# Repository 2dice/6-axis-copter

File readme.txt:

■6軸コプター概要
6軸に移動可能なマルチコプターを6個のプロペラで実現することを目標としている．
最終的には自動で衝突回避・PCからコマンドを受信しアクロバットな動きをさせる．

■開発フェーズ
ラフ設計段階
・電子回路
	1x基板(コアレス->ブラシモータ)浮力不足により2xでブラシレスモータ試作
	2x基板作成中
・アクチュエータ
	ブラシレスモータ・プロペラ仮選定済み．2xで浮力確認
・ソフトウェア
	デバイスドライバ仮実装完了．
	2x基板作成後最終確認．その後モータ制御実装．
・筐体
	2x向け設計完了(3Dプリント中)

■ディレクトリ構成
./datasheet
	電子回路に使用している部品のデータシート置き場
./devlog
	開発記録
./schematic
	**.sch
		回路図(kicad)
	**.kicad_pcb
		基板図(kicad)
	librarys
		回路図に使用したライブラリ(kicad)
	gbr
		P板.com提出ファイル(板厚0.6mmで発注)
	**.pdf
		回路図
	**.FCStd
		筐体3D-CAD設計ファイル(FreeCAD)
	**.stl
		DMM.make提出ファイル(3Dプリンタ用STLファイル)
./src
	ソフトウェア
	環境構築は以下を参照
	http://qiita.com/2dice/items/70c5abf6259508660bce
./src/tools/6-axis-monitor
	無線通信(zigbee)によるモニタツール(Qt)
	zigbee環境構築方法は作成中

■構成
・プロペラ配置は3d図面及び./devlog/pictureを参照
・ブラシレスモータとリポバッテリ(3セル直列)を使用
・移動量は3軸ジャイロ及び3軸加速度センサでモニタ
・EEPROMにチューニングパラメータを保存
・測距センサを全軸に付け，衝突を回避するようなロジックを入れる
・デバイスの電源電圧の都合上4.5V/3.6Vの2電源を生成．
  本来I/Fにレベルシフタを入れるべきだが抵抗で保護し実力で故障回避を狙う．
  そのため電源電圧を極力近づける設計とした．

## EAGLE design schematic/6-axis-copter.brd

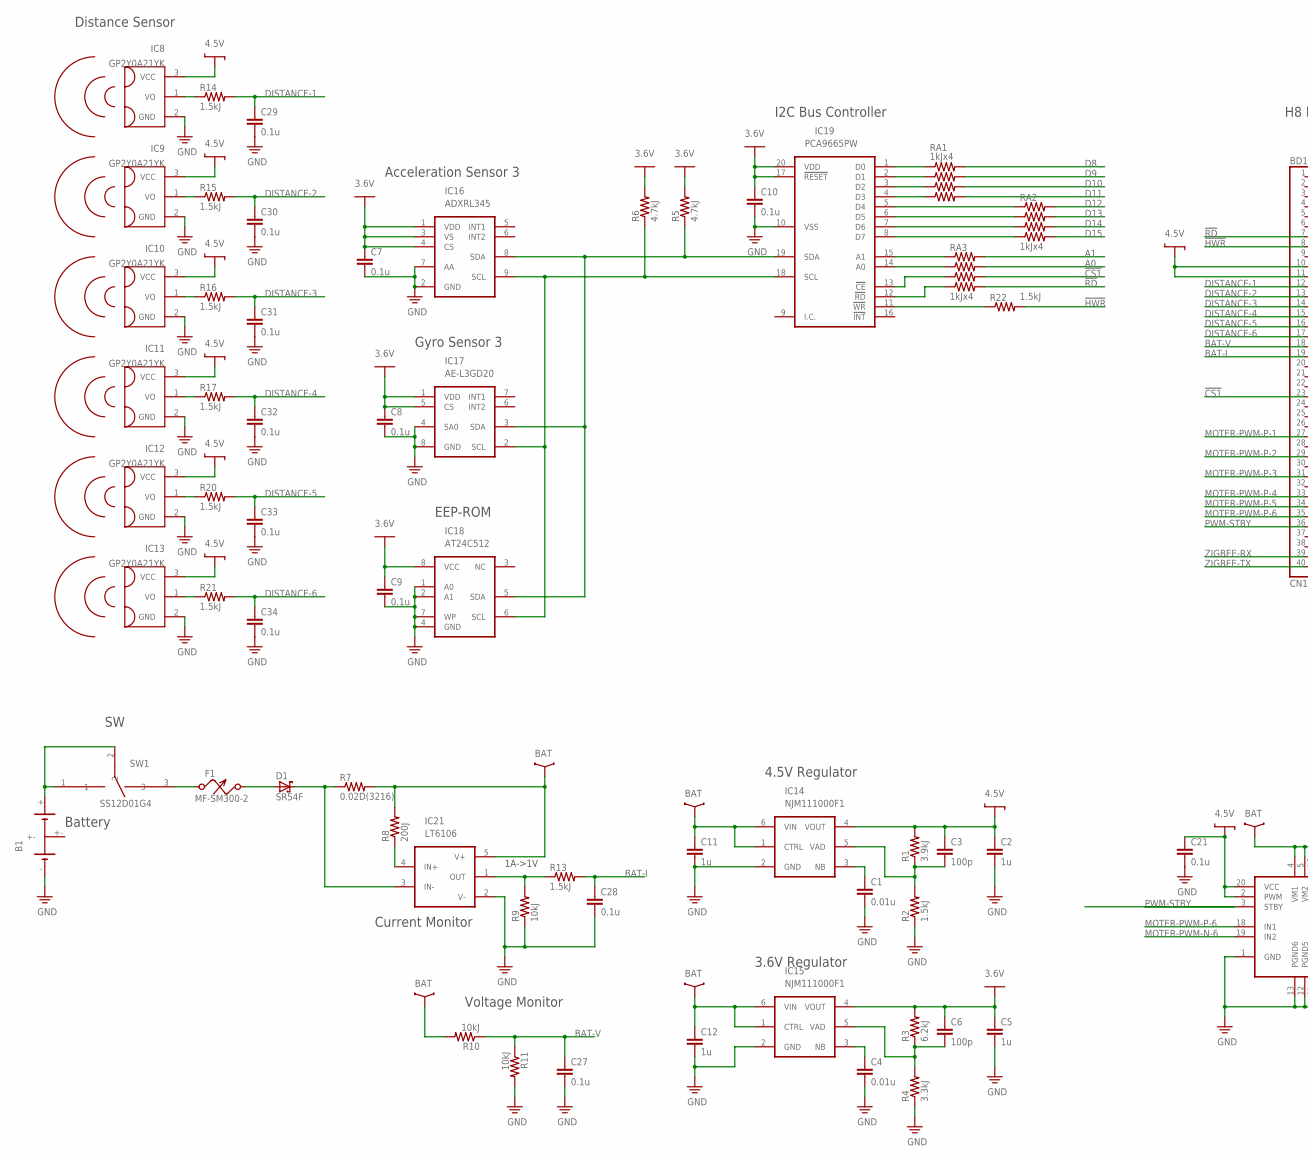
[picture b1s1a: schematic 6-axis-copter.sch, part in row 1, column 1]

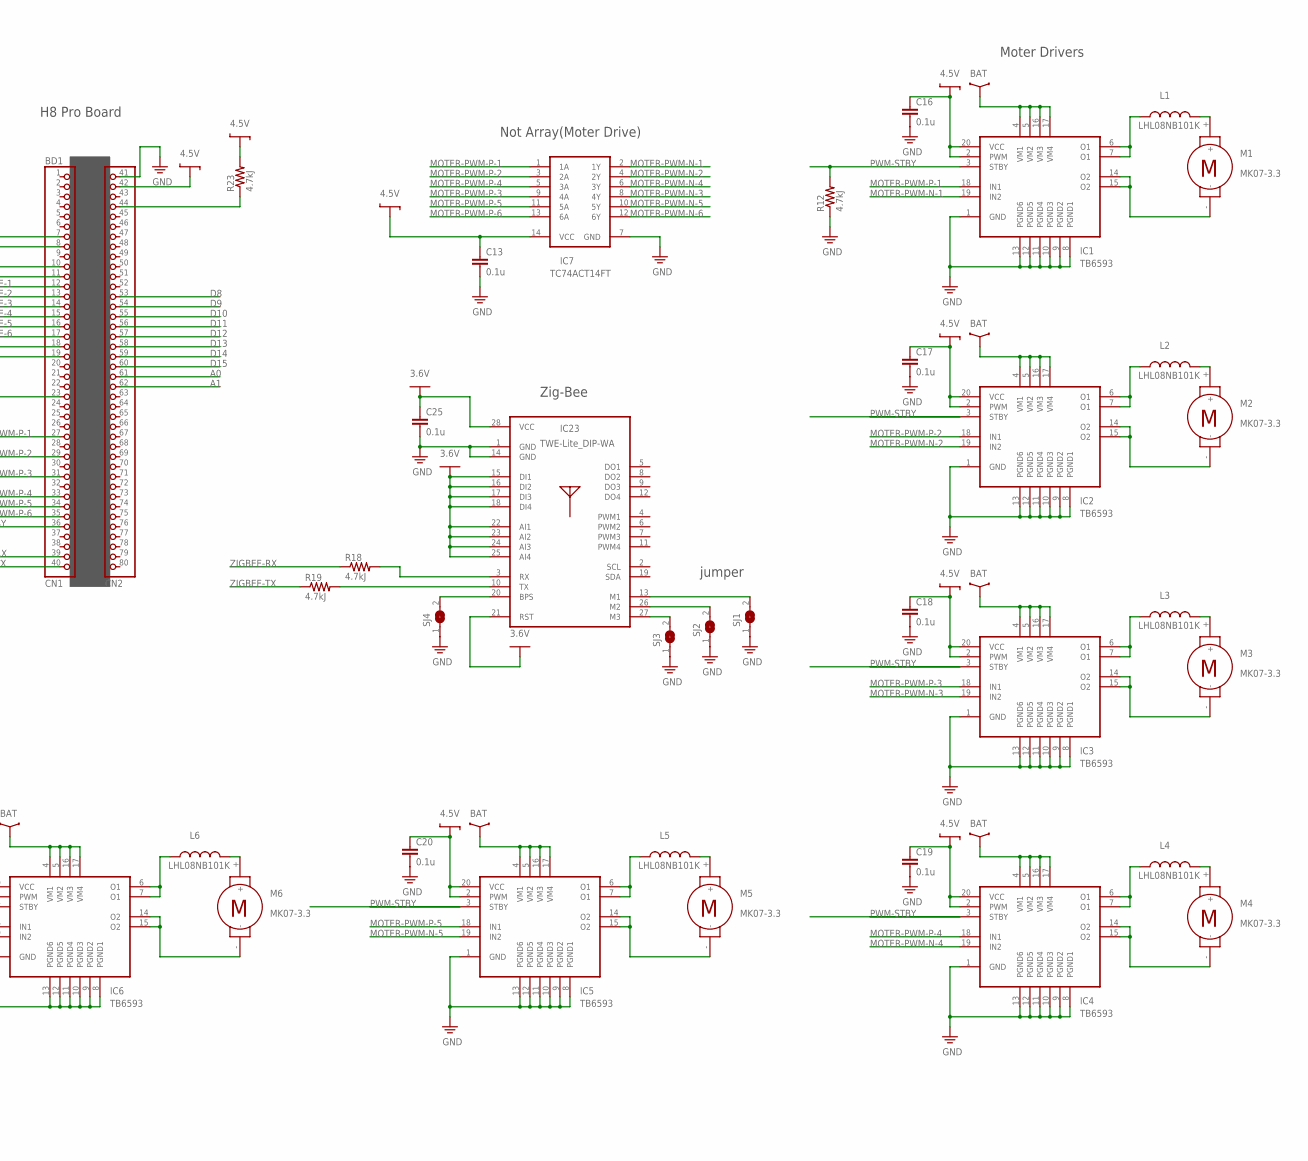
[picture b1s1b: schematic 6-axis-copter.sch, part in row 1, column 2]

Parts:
B1: LIPO-BATT; LIPO2CEL
BD1: H8-PRO-BOARD
C1, C4: 0.01u; C1608
C2, C5, C11, C12: 1u; C1608
C3, C6: 100p; C1608
C7, C8, C9, C10, C13, C16, C17, C18, C19, C20, C21, C25, C27, C28, C29, C30, C31, C32, C33, C34: 0.1u; C1608
D1: SR54F; SMBF
F1: MF-SM300-2
IC1, IC2, IC3, IC4, IC5, IC6: TB6593FNG; SSOP20-0.65
IC7: TC74ACT14FT; TSSOP14-0.65
IC8, IC9, IC10, IC11, IC12, IC13: GP2Y0A21YK; DUMMY-GP2Y0A21YK
IC14, IC15: NJM111000F1; SOT23-6-0.95
IC16: ADXL345; DIP9-2.54
IC17: AE-L3GD20; DIP8-2.54
IC18: AT24C512; DIP8-2.54
IC19: PCA9665PW; SSOP20-0.65
IC21: LT6106; TSOT23-5-0.95
IC23: TWE-LITE-DIP-WA; DIP28-2.54
L1, L2, L3, L4, L5, L6: LHL08NB101K; LHL08
M1, M2, M3, M4, M5, M6: MK07-3.3; DUMMY-MK07
R1: 3.9kJ; C1608
R2, R13, R14, R15, R16, R17, R20, R21, R22: 1.5kJ; C1608
R3: 6.2kJ; C1608
R4: 3.3kJ; C1608
R5, R6, R12, R18, R19, R23: 4.7kJ; C1608
R7: 0.02D(3216); R3216
R8: 200J; C1608
R9, R10, R11: 10kJ; C1608
RA1, RA2, RA3: 1kJx4; BCN164AB
SJ1, SJ2, SJ3, SJ4: SJ
SW1: SS12D01G4

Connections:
3.6V: C5.1, C6.1, C7.1, C8.1, C9.1, C10.1, C25.1, IC15.4 (VOUT), IC16.1 (VDD), IC16.3 (VS), IC16.4 (CS), IC17.1 (VDD), IC17.5 (CS), IC18.8 (VCC), IC19.17 (!RESET), IC19.20 (VDD), IC23.15 (DI1), IC23.16 (DI2), IC23.17 (DI3), IC23.18 (DI4), IC23.21 (RST), IC23.22 (AI1), IC23.23 (AI2), IC23.24 (AI3), IC23.25 (AI4), IC23.28 (VCC), R3.2, R5.2, R6.2
4.5V: BD1.10 (1-10), BD1.11 (1-11), BD1.42 (2-2), C2.1, C3.1, C13.1, C16.1, C17.1, C18.1, C19.1, C20.1, C21.1, IC1.2 (PWM), IC1.20 (VCC), IC2.2 (PWM), IC2.20 (VCC), IC3.2 (PWM), IC3.20 (VCC), IC4.2 (PWM), IC4.20 (VCC), IC5.2 (PWM), IC5.20 (VCC), IC6.2 (PWM), IC6.20 (VCC), IC7.14 (VCC), IC8.3 (VCC), IC9.3 (VCC), IC10.3 (VCC), IC11.3 (VCC), IC12.3 (VCC), IC13.3 (VCC), IC14.4 (VOUT), R1.2, R23.2
!CS1: BD1.23 (1-23), RA3.6
!HWR: BD1.8 (1-8), R22.2
!IRQ5: BD1.44 (2-4), R23.1
!RD: BD1.7 (1-7), RA3.5
A0: BD1.61 (2-21), RA3.7
A1: BD1.62 (2-22), RA3.8
BAT: C11.1, C12.1, IC1.4 (VM1), IC1.5 (VM2), IC1.16 (VM3), IC1.17 (VM4), IC2.4 (VM1), IC2.5 (VM2), IC2.16 (VM3), IC2.17 (VM4), IC3.4 (VM1), IC3.5 (VM2), IC3.16 (VM3), IC3.17 (VM4), IC4.4 (VM1), IC4.5 (VM2), IC4.16 (VM3), IC4.17 (VM4), IC5.4 (VM1), IC5.5 (VM2), IC5.16 (VM3), IC5.17 (VM4), IC6.4 (VM1), IC6.5 (VM2), IC6.16 (VM3), IC6.17 (VM4), IC14.1 (CTRL), IC14.6 (VIN), IC15.1 (CTRL), IC15.6 (VIN), IC21.5 (V+), R7.2, R8.2, R10.2
BAT-I: BD1.19 (1-19), C28.1, R13.2
BAT-V: BD1.18 (1-18), C27.1, R10.1, R11.1
D8: BD1.53 (2-13), RA1.8
D9: BD1.54 (2-14), RA1.7
D10: BD1.55 (2-15), RA1.6
D11: BD1.56 (2-16), RA1.5
D12: BD1.57 (2-17), RA2.8
D13: BD1.58 (2-18), RA2.7
D14: BD1.59 (2-19), RA2.6
D15: BD1.60 (2-20), RA2.5
DISTANCE-1: BD1.12 (1-12), C29.1, R14.2
DISTANCE-2: BD1.13 (1-13), C30.1, R15.2
DISTANCE-3: BD1.14 (1-14), C31.1, R16.2
DISTANCE-4: BD1.15 (1-15), C32.1, R17.2
DISTANCE-5: BD1.16 (1-16), C33.1, R20.2
DISTANCE-6: BD1.17 (1-17), C34.1, R21.2
GND: B1.-, BD1.41 (2-1), C1.2, C2.2, C4.2, C5.2, C7.2, C8.2, C9.2, C10.2, C11.2, C12.2, C13.2, C16.2, C17.2, C18.2, C19.2, C20.2, C21.2, C25.2, C27.2, C28.2, C29.2, C30.2, C31.2, C32.2, C33.2, C34.2, IC1.1 (GND), IC1.8 (PGND1), IC1.9 (PGND2), IC1.10 (PGND3), IC1.11 (PGND4), IC1.12 (PGND5), IC1.13 (PGND6), IC2.1 (GND), IC2.8 (PGND1), IC2.9 (PGND2), IC2.10 (PGND3), IC2.11 (PGND4), IC2.12 (PGND5), IC2.13 (PGND6), IC3.1 (GND), IC3.8 (PGND1), IC3.9 (PGND2), IC3.10 (PGND3), IC3.11 (PGND4), IC3.12 (PGND5), IC3.13 (PGND6), IC4.1 (GND), IC4.8 (PGND1), IC4.9 (PGND2), IC4.10 (PGND3), IC4.11 (PGND4), IC4.12 (PGND5), IC4.13 (PGND6), IC5.1 (GND), IC5.8 (PGND1), IC5.9 (PGND2), IC5.10 (PGND3), IC5.11 (PGND4), IC5.12 (PGND5), IC5.13 (PGND6), IC6.1 (GND), IC6.8 (PGND1), IC6.9 (PGND2), IC6.10 (PGND3), IC6.11 (PGND4), IC6.12 (PGND5), IC6.13 (PGND6), IC7.7 (GND), IC8.2 (GND), IC9.2 (GND), IC10.2 (GND), IC11.2 (GND), IC12.2 (GND), IC13.2 (GND), IC14.2 (GND), IC15.2 (GND), IC16.2 (GND), IC16.7 (AA), IC17.4 (SA0), IC17.8 (GND), IC18.1 (A0), IC18.2 (A1), IC18.4 (GND), IC18.7 (WP), IC19.10 (VSS), IC21.2 (V-), IC23.1 (GND), IC23.14 (GND), R2.1, R4.1, R9.1, R11.2, R12.1, SJ1.1, SJ2.1, SJ3.1, SJ4.1
MOTER-PWM-N-1: IC1.19 (IN2), IC7.2 (1Y)
MOTER-PWM-N-2: IC2.19 (IN2), IC7.4 (2Y)
MOTER-PWM-N-3: IC3.19 (IN2), IC7.8 (4Y)
MOTER-PWM-N-4: IC4.19 (IN2), IC7.6 (3Y)
MOTER-PWM-N-5: IC5.19 (IN2), IC7.10 (5Y)
MOTER-PWM-N-6: IC6.19 (IN2), IC7.12 (6Y)
MOTER-PWM-P-1: BD1.27 (1-27), IC1.18 (IN1), IC7.1 (1A)
MOTER-PWM-P-2: BD1.29 (1-29), IC2.18 (IN1), IC7.3 (2A)
MOTER-PWM-P-3: BD1.31 (1-31), IC3.18 (IN1), IC7.9 (4A)
MOTER-PWM-P-4: BD1.33 (1-33), IC4.18 (IN1), IC7.5 (3A)
MOTER-PWM-P-5: BD1.34 (1-34), IC5.18 (IN1), IC7.11 (5A)
MOTER-PWM-P-6: BD1.35 (1-35), IC6.18 (IN1), IC7.13 (6A)
unnamed: IC1.6 (O1), IC1.7 (O1), L1.1
unnamed: IC1.14 (O2), IC1.15 (O2), M1.-
unnamed: IC2.6 (O1), IC2.7 (O1), L2.1
unnamed: IC2.14 (O2), IC2.15 (O2), M2.-
unnamed: IC3.6 (O1), IC3.7 (O1), L3.1
unnamed: IC3.14 (O2), IC3.15 (O2), M3.-
unnamed: IC4.6 (O1), IC4.7 (O1), L4.1
unnamed: IC4.14 (O2), IC4.15 (O2), M4.-
unnamed: IC5.6 (O1), IC5.7 (O1), L5.1
unnamed: IC5.14 (O2), IC5.15 (O2), M5.-
unnamed: IC6.6 (O1), IC6.7 (O1), L6.1
unnamed: IC6.14 (O2), IC6.15 (O2), M6.-
unnamed: L1.2, M1.+
unnamed: C1.1, IC14.3 (NB)
unnamed: C3.2, IC14.5 (VAD), R1.1, R2.2
unnamed: D1.1 (C), IC21.3 (IN-), R7.1
unnamed: C4.1, IC15.3 (NB)
unnamed: C6.2, IC15.5 (VAD), R3.1, R4.2
unnamed: IC16.8 (SDA), IC17.3 (SDA), IC18.5 (SDA), IC19.19 (SDA), R5.1
unnamed: IC16.9 (SCL), IC17.2 (SCL), IC18.6 (SCL), IC19.18 (SCL), R6.1
unnamed: IC21.4 (IN+), R8.1
unnamed: D1.2 (A), F1.2
unnamed: B1.+, SW1.1, SW1.2
unnamed: IC23.3 (RX), R18.2
unnamed: L2.2, M2.+
unnamed: L3.2, M3.+
unnamed: L4.2, M4.+
unnamed: IC23.27 (M3), SJ3.2
unnamed: IC23.26 (M2), SJ2.2
unnamed: IC23.13 (M1), SJ1.2
unnamed: IC23.20 (BPS), SJ4.2
unnamed: IC21.1 (OUT), R9.2, R13.1
unnamed: IC23.10 (TX), R19.2
unnamed: IC9.1 (VO), R15.1
unnamed: L5.2, M5.+
unnamed: IC8.1 (VO), R14.1
unnamed: IC10.1 (VO), R16.1
unnamed: L6.2, M6.+
unnamed: F1.1, SW1.3
unnamed: IC12.1 (VO), R20.1
unnamed: IC11.1 (VO), R17.1
unnamed: IC13.1 (VO), R21.1
unnamed: IC19.1 (D0), RA1.1
unnamed: IC19.2 (D1), RA1.2
unnamed: IC19.3 (D2), RA1.3
unnamed: IC19.4 (D3), RA1.4
unnamed: IC19.5 (D4), RA2.1
unnamed: IC19.6 (D5), RA2.2
unnamed: IC19.7 (D6), RA2.3
unnamed: IC19.8 (D7), RA2.4
unnamed: IC19.15 (A1), RA3.1
unnamed: IC19.14 (A0), RA3.2
unnamed: IC19.13 (!CE), RA3.3
unnamed: IC19.12 (!RD), RA3.4
unnamed: IC19.11 (!WR), R22.1
PWM-STBY: BD1.36 (1-36), IC1.3 (STBY), IC2.3 (STBY), IC3.3 (STBY), IC4.3 (STBY), IC5.3 (STBY), IC6.3 (STBY), R12.2
ZIGBEE-RX: BD1.39 (1-39), R18.1
ZIGBEE-TX: BD1.40 (1-40), R19.1

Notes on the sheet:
1A->1V
Current Monitor
Voltage Monitor
4.5V Regulator
3.6V Regulator
Battery
Distance Sensor
Acceleration Sensor 3
Gyro Sensor 3
EEP-ROM
I2C Bus Controller
Moter Drivers
Not Array(Moter Drive)
jumper
Zig-Bee
H8 Pro Board

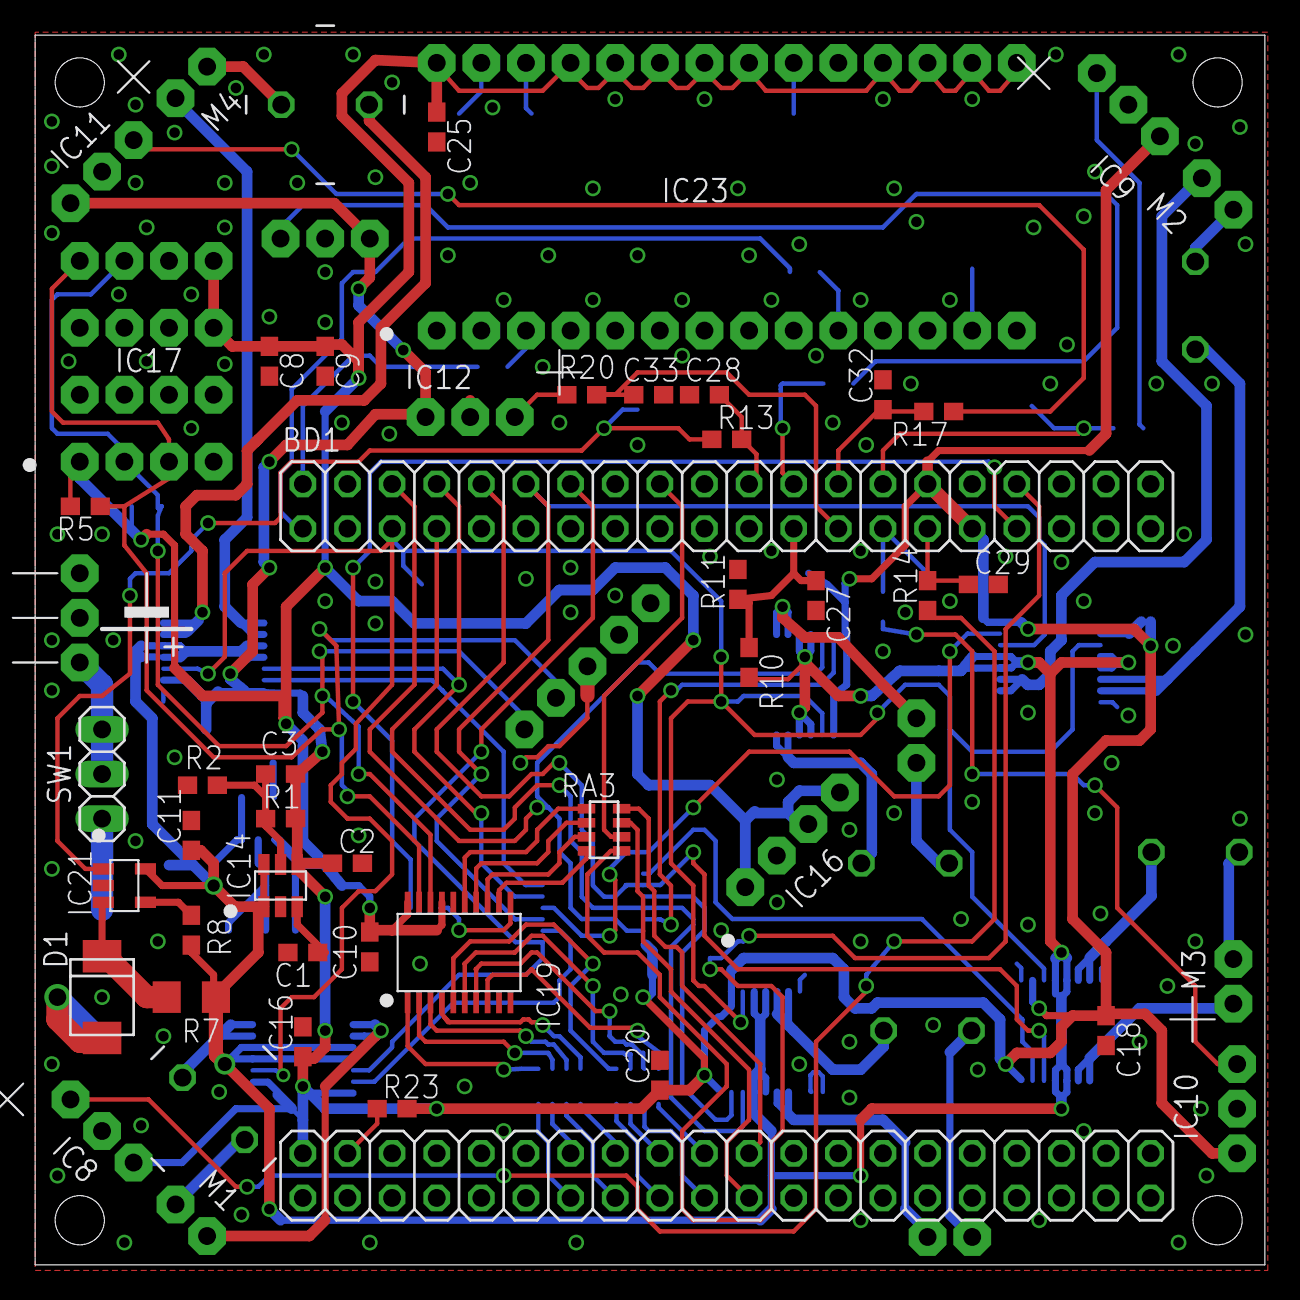
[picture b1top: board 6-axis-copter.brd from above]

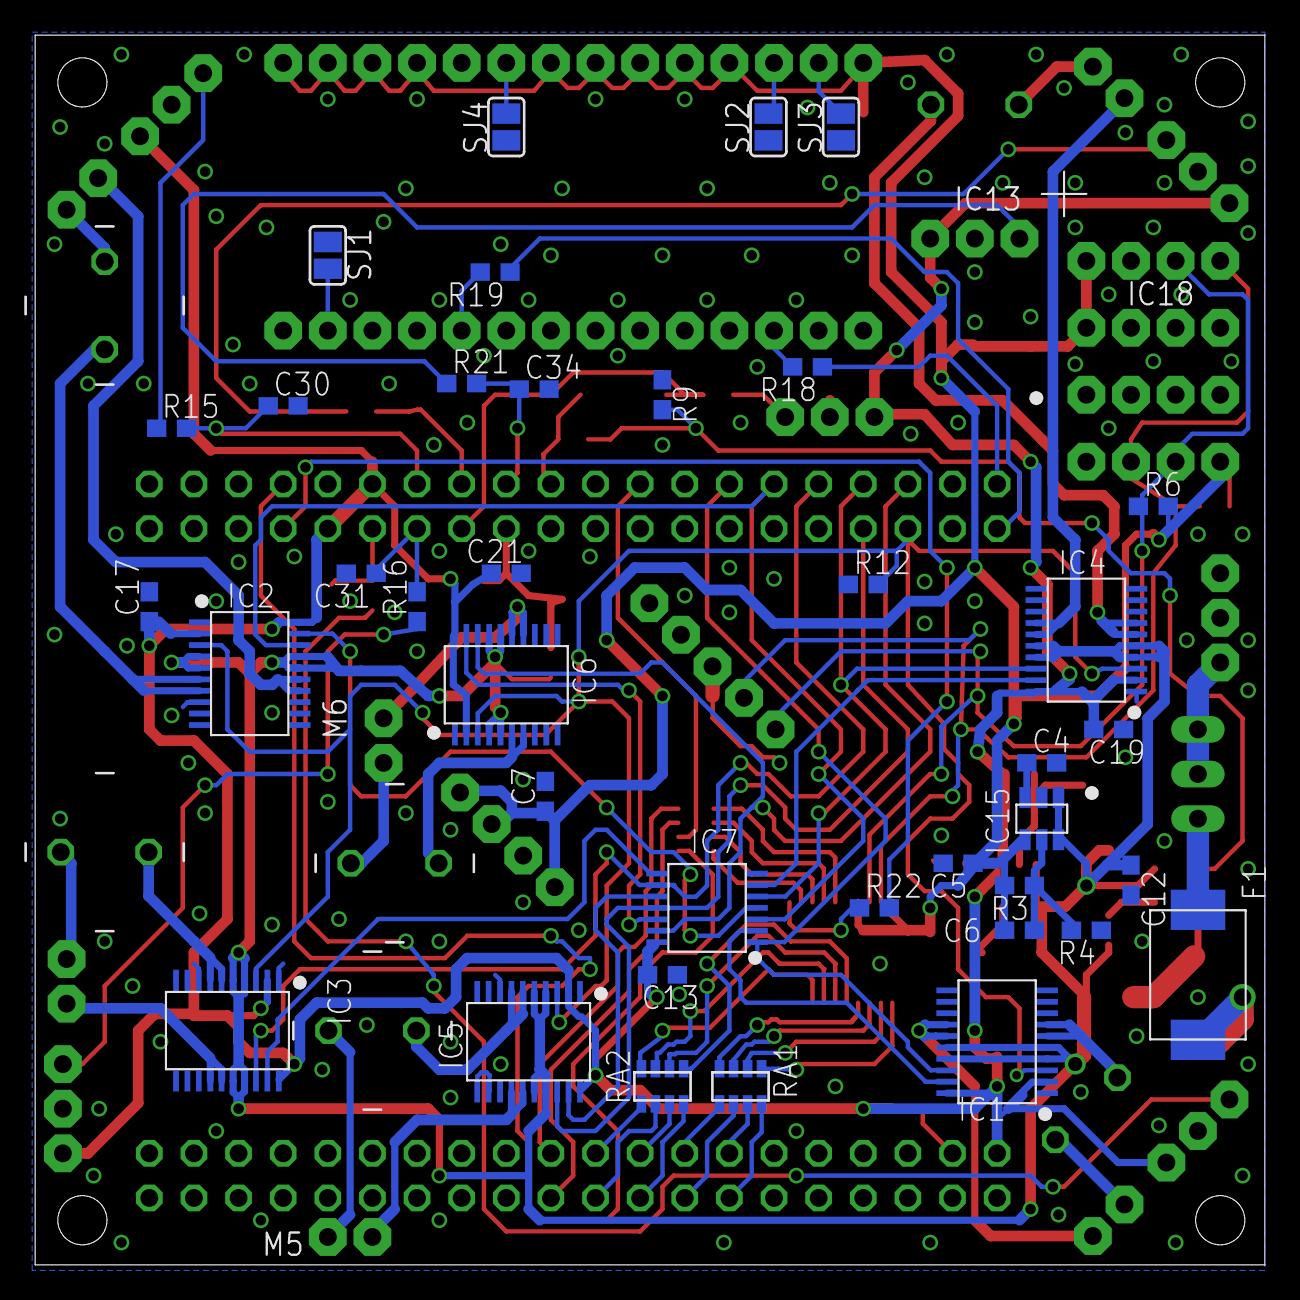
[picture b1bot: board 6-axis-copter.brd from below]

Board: 2 copper layers, 70.0 x 70.0 mm, 96 parts (46 on the bottom side), 96 nets.

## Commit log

2014-08-23 書き込みテスト serialでhello worldを返すプログラム．水晶発振子25MHzでの書き込みテスト
2014-08-24 前プロジェクトを元にリファクタリング,VA=PA転送実装
2014-08-24 DRAM実装
2014-08-24 timer/timer割り込み実装
2014-08-24 周辺情報更新
2014-08-30 TIOCA0にPWM出力を実装
2014-08-30 TIOCA1にPWM出力を実装
2014-08-30 TIOCA2にPWM出力を実装
2014-08-30 TMO0にPWM出力を実装
2014-08-30 TMIO1にPWM出力を実装
2014-08-30 TMO2にPWM出力を実装
2014-08-31 makeでTAGSファイルを生成するようMakefileを修正
2014-08-31 IRQ5にプルアップ抵抗追加(オープンドレイン)
2014-09-06 回路図の不要な配線を削除
2014-09-07 AN0のAD値取得を実装
2014-09-08 AN1のAD値取得を実装
2014-09-08 リファクタリング(ADチャネルセレクトを汎用関数に切り出し)
2014-09-08 AN2~7のAD値取得を実装
2014-09-08 timer_init()からモータドライバの初期化を切り出してenable出力を追加
2014-09-15 I2Cバスコントローラ/加速度センサのデバイス情報追加
2014-09-15 TAGSファイルを生成する際に削除してから生成するように変更
2014-09-17 SCI2にzigbeeシリアル送信実装
2014-09-18 zigbeeからのコマンド受信割り込み実装
2014-09-20 SCI0をSCI1という記述に修正 SCI1に対し勘違いしてSCI0という名前をつけていたため
2014-10-04 I2Cバスコン及び加速度センサからのデータ読み出しを実装
2014-10-05 角速度センサからのデータ読み出しを実装
2014-10-05 リファクタリング(I2Cからの連続2バイト読みだし関数の変数名を汎用化)
2014-10-05 周辺情報の進捗更新
2014-10-05 角速度センサの読み出しを2バイト読み出しに変更
2014-10-05 モニタツール first commit(コンソールにD1の値のみを表示)
2014-10-05 モニタツールにD1を出力する簡易グラフ実装
2014-10-06 モニタツールで16進加速度データを物理値にして出力できるよう変更
2014-10-06 リファクタリング(データ格納関数を分離)
2014-10-06 モニタツールに全ての受信データ取り込みを実装
2014-10-08 モニタツールのAXにゼロ点補正と速度・距離計算を仮実装
2014-10-09 モニタツールの速度計算をブールの公式で再実装
2014-10-09 モニタツールに角度算出を実装(ブールの公式)
2014-10-11 回路図の配線ミスを修正
2014-10-11 回路図のバッテリーシンボル・フットプリント修正
2014-10-11 回路図のH8ボードフットプリントを修正
2014-10-11 回路図のモーターに直列にコイル追加
2014-10-11 回路図：DIP部品のサイズ修正
2014-10-11 回路図にバッテリーSW追加
2014-10-14 PCBボード図作成
2014-10-15 基板製造メーカー(P板.com)の指摘を元にPCBボード図を修正
2014-10-18 部品表作成
2014-10-18 readmeの進捗，ディレクトリ構成を更新
2014-10-26 周辺情報更新(筐体設計変更)
2014-10-31 周辺情報更新(筐体設計再変更)
2014-11-05 筐体仮作成
2014-11-08 筐体ASSY用スタンド作成
2014-11-13 モニタツールをQtで実装開始 シリアル入力をデバッグコンソールに出力
2014-11-14 モニタツール：シリアルのpublic変数・関数を極力privateに隠蔽
2014-11-15 dataクラス実装 serial_ifで受け取ったデータをdataクラスへ渡し格納
2014-11-16 モニタツール：シリアルデータの取りこぼしをなくすよう修正
2014-11-28 モニタツール：QMLでZ軸の加速度をグラフ表示 scene graphのサンプルコード"graph"をベースに作成
2014-11-29 浮力不足によりブラシレスモータに方針転換
2014-12-13 ブラシレスモータドライバデータシートまとめ
2015-01-10 モータ回転成功，浮力不足のためドライバ再選定が必要
2015-02-01 DRV11873で再挑戦．モータ回転せず，ドライバ再々選定が必要
2015-02-28 TB6588で再挑戦．ある程度浮力が出たため2x基板を作成(基板CADをkicadに変更)
2015-03-02 3Dプリンタ用筐体仮設計
2015-03-22 3Dプリンタ用筐体データ作成
2015-03-28 2x基板部品実装完了
2015-03-28 モニタツール：シリアルデータの取りこぼしを軽減
2015-03-29 10msで取得したセンサ値を80msで平均してシリアル出力する処理を実装
2015-04-04 モータdutyのgetter,setter実装
2015-04-04 UVLO実装
2015-04-29 バッテリ2S->3Sに変更しホバー仮実装．筐体破損のため再設計
2015-05-01 モニタツール：グラフを増殖しパネル状に配置
2015-06-13 筐体衝突時のモータ停止(OverShockLockOut)実装
2015-06-13 4.5V低下・モーター脱調を軽減するためハード改造 負荷が大きすぎたため5Vレギュレータ変更． モータードライバのカレントリミットを積分&回転数変動時の応答速度を遅くしモーター脱調を軽減． 電圧低下を軽減するためリポバッテリの容量増加しモーター直列に抵抗追加． 軽量化のため基板のNC_DIP_pin抜き&筐体足切断し縫い糸で補強
2015-06-20 姿勢制御に使用するセンサ値を平均値から移動平均値に変更
2015-06-20 姿勢制御に角速度センサ値を追加し回転抑制する処理を追加
2015-06-20 加速度センサ初期値を実測値から決定
2015-06-20 モニタツール：データ受信がなければグラフの更新を停止するように変更
2015-06-21 モニタツール：コマンド送信ボタン実装
